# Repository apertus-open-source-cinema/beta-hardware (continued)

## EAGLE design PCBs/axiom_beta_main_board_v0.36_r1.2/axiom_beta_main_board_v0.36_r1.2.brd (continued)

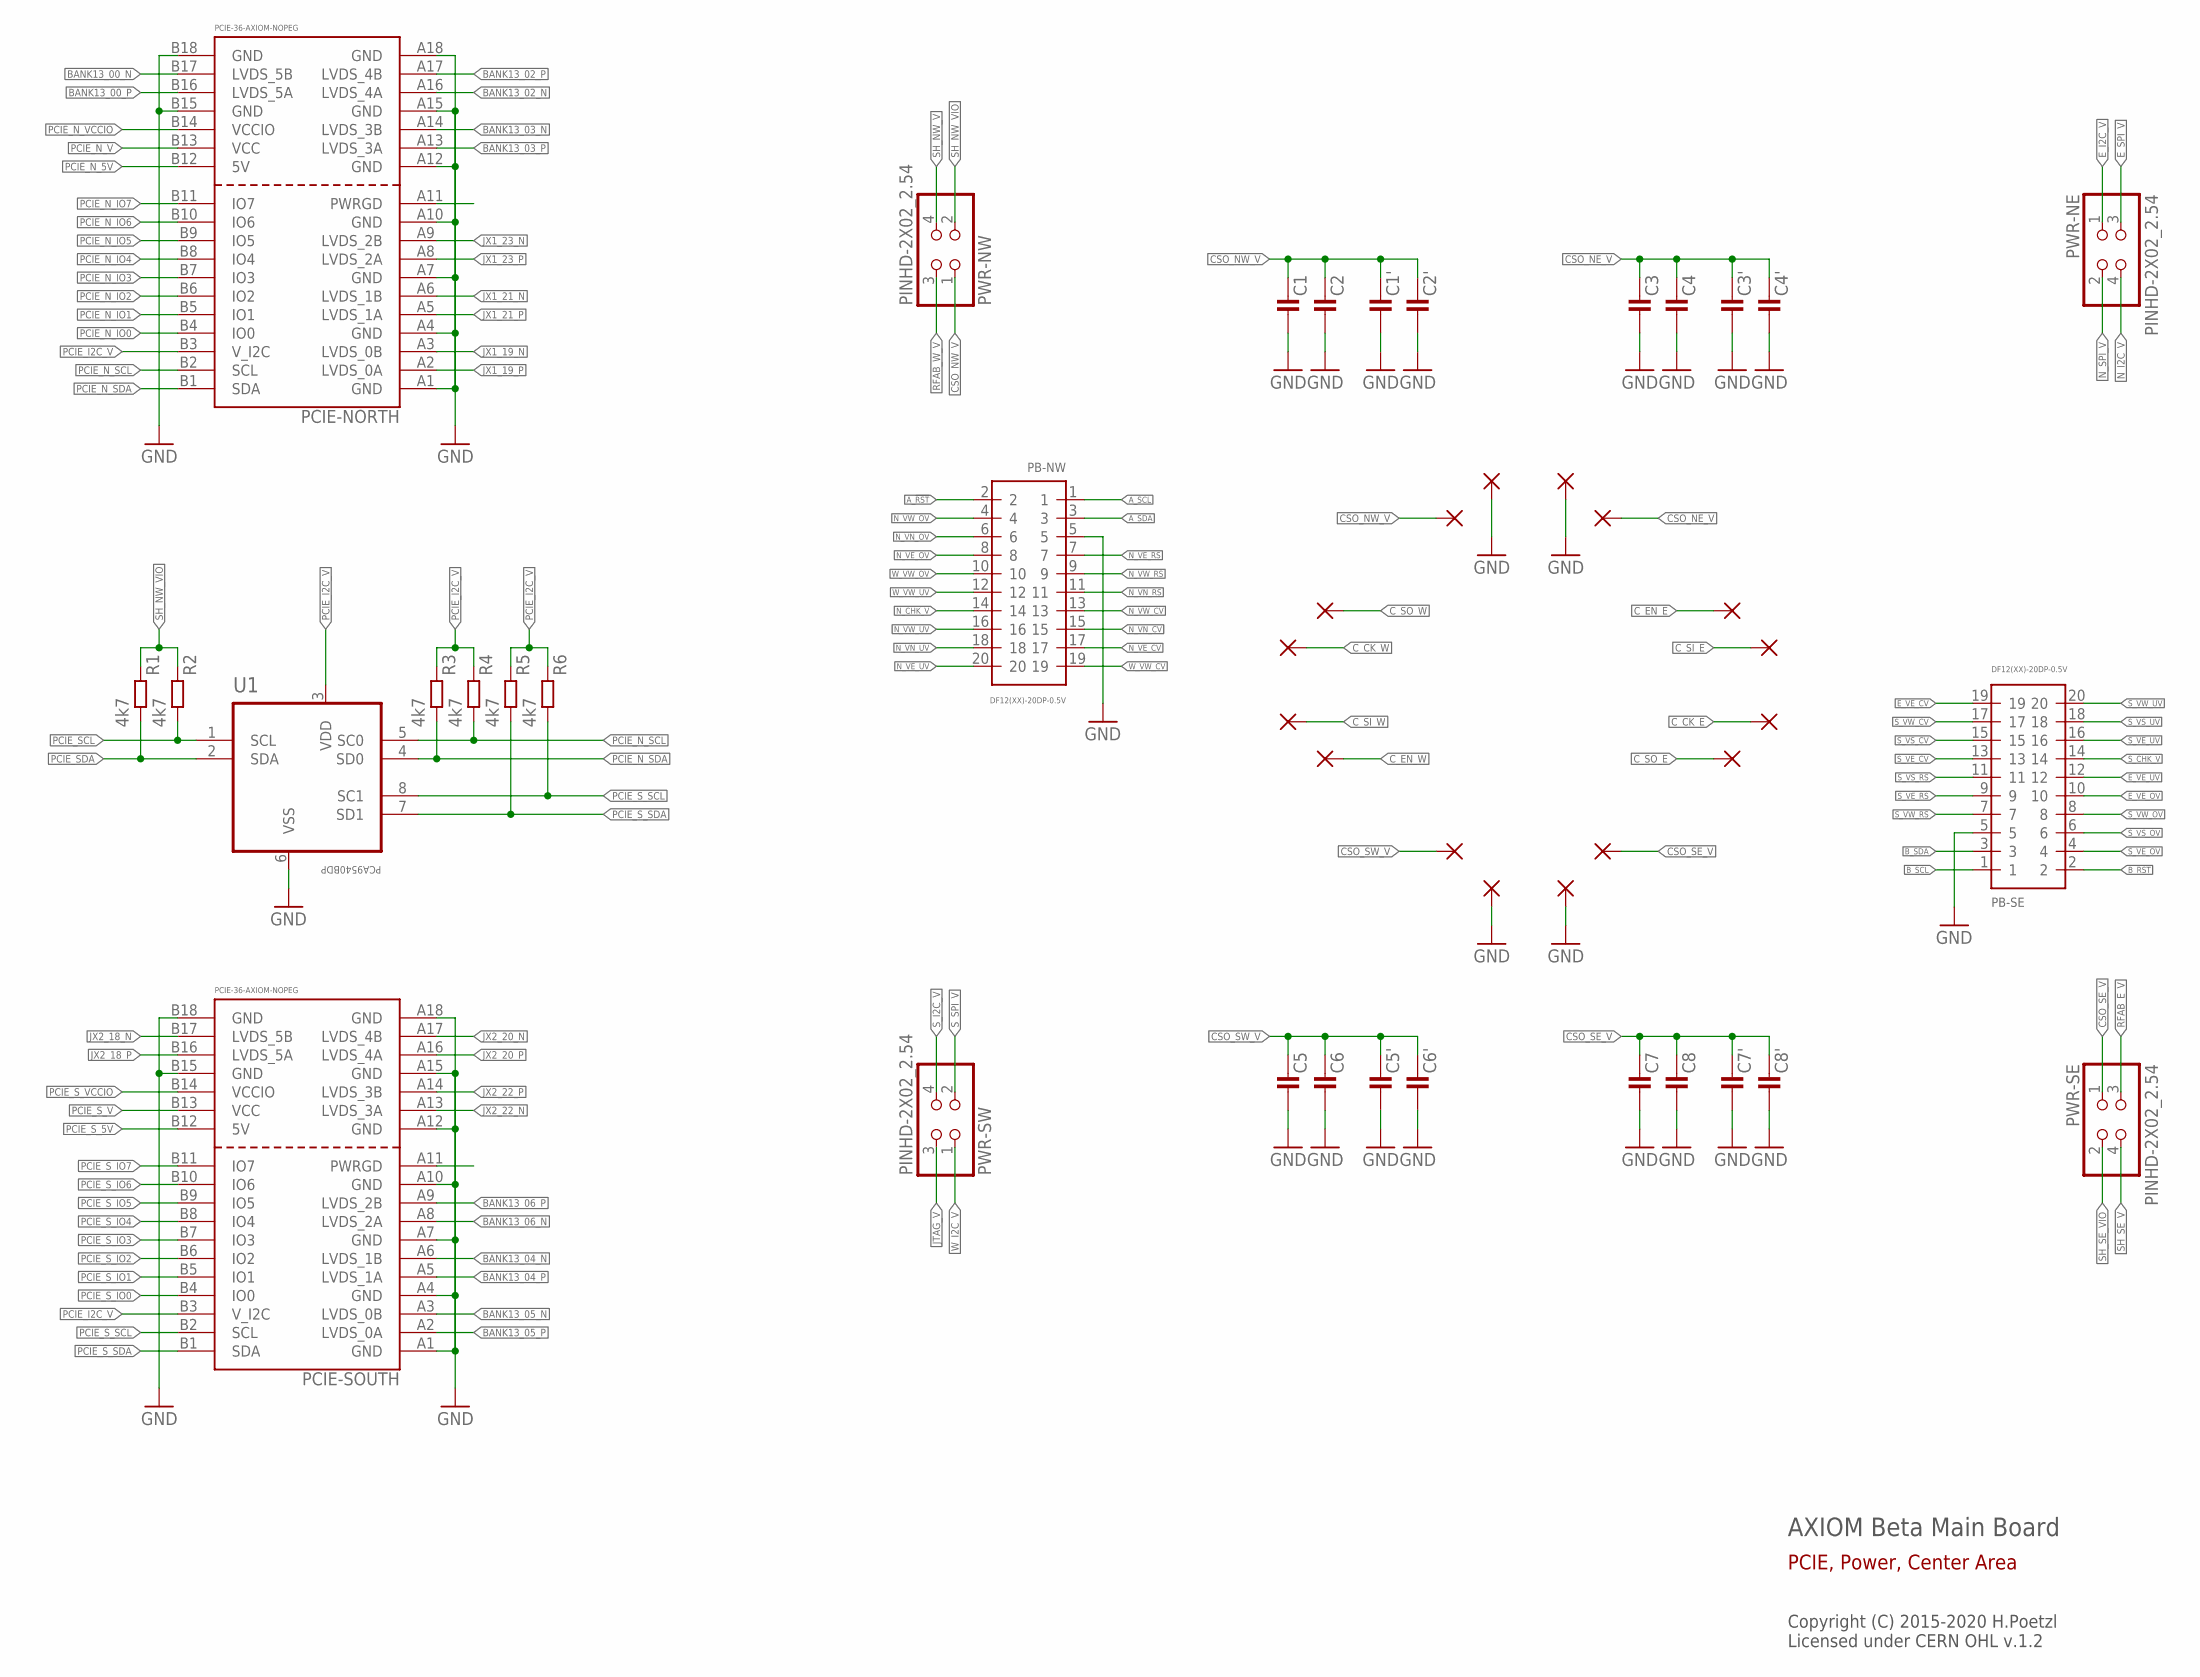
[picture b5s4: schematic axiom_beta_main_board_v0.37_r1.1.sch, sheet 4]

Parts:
C1, C1', C3, C3', C5, C5', C7, C7': C0805-A; 0805-A
C2, C2', C4, C4', C6, C6', C8, C8': C0603-A; 0603-A
PAD1, PAD2, PAD3, PAD4, PAD5, PAD6, PAD7, PAD8, PAD9, PAD10, PAD11, PAD12, PAD13, PAD14, PAD15, PAD16: PINPAD1.27MM; 1.2/0.6
PB-NW: DF12(XX)-20DP-0.5V
PB-SE: DF12(XX)-20DP-0.5V
PCIE-NORTH: PCIE-36-AXIOM-NOPEG; PCIE-36-NOPEG
PCIE-SOUTH: PCIE-36-AXIOM-NOPEG; PCIE-36-NOPEG
PWR-NE: PINHD-2X02_2.54; 2X02
PWR-NW: PINHD-2X02_2.54; 2X02
PWR-SE: PINHD-2X02_2.54; 2X02
PWR-SW: PINHD-2X02_2.54; 2X02
R1, R2, R3, R4, R5, R6: 4k7; 0402-B
U1: PCA9540BDP; SOP65P490X300-8N

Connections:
A_!RST: PB-NW.2; also elsewhere on the board
A_SCL: PB-NW.1; also elsewhere on the board
A_SDA: PB-NW.3; also elsewhere on the board
BANK13_00_N: PCIE-NORTH.B17 (LVDS_5B); also elsewhere on the board
BANK13_00_P: PCIE-NORTH.B16 (LVDS_5A); also elsewhere on the board
BANK13_02_N: PCIE-NORTH.A16 (LVDS_4A); also elsewhere on the board
BANK13_02_P: PCIE-NORTH.A17 (LVDS_4B); also elsewhere on the board
BANK13_03_N: PCIE-NORTH.A14 (LVDS_3B); also elsewhere on the board
BANK13_03_P: PCIE-NORTH.A13 (LVDS_3A); also elsewhere on the board
BANK13_04_N: PCIE-SOUTH.A6 (LVDS_1B); also elsewhere on the board
BANK13_04_P: PCIE-SOUTH.A5 (LVDS_1A); also elsewhere on the board
BANK13_05_N: PCIE-SOUTH.A3 (LVDS_0B); also elsewhere on the board
BANK13_05_P: PCIE-SOUTH.A2 (LVDS_0A); also elsewhere on the board
BANK13_06_N: PCIE-SOUTH.A8 (LVDS_2A); also elsewhere on the board
BANK13_06_P: PCIE-SOUTH.A9 (LVDS_2B); also elsewhere on the board
B_!RST: PB-SE.2; also elsewhere on the board
B_SCL: PB-SE.1; also elsewhere on the board
B_SDA: PB-SE.3; also elsewhere on the board
CSO_NE_V: C3.1, C3'.1, C4.1, C4'.1, PAD2.1; also elsewhere on the board
CSO_NW_V: C1.1, C1'.1, C2.1, C2'.1, PAD15.1, PWR-NW.1
CSO_SE_V: C7.1, C7'.1, C8.1, C8'.1, PAD7.1, PWR-SE.1
CSO_SW_V: C5.1, C5'.1, C6.1, C6'.1, PAD10.1; also elsewhere on the board
C_CK_E: PAD5.1; also elsewhere on the board
C_CK_W: PAD13.1; also elsewhere on the board
C_EN_E: PAD3.1; also elsewhere on the board
C_EN_W: PAD11.1; also elsewhere on the board
C_SI_E: PAD4.1; also elsewhere on the board
C_SI_W: PAD12.1; also elsewhere on the board
C_SO_E: PAD6.1; also elsewhere on the board
C_SO_W: PAD14.1; also elsewhere on the board
E_I2C_V: PWR-NE.1; also elsewhere on the board
E_SPI_V: PWR-NE.3; also elsewhere on the board
E_VE_CV: PB-SE.19; also elsewhere on the board
E_VE_OV: PB-SE.10; also elsewhere on the board
E_VE_UV: PB-SE.12; also elsewhere on the board
GND: C1.2, C1'.2, C2.2, C2'.2, C3.2, C3'.2, C4.2, C4'.2, C5.2, C5'.2, C6.2, C6'.2, C7.2, C7'.2, C8.2, C8'.2, PAD1.1, PAD8.1, PAD9.1, PAD16.1, PB-NW.5, PB-SE.5, PCIE-NORTH.A1 (GND), PCIE-NORTH.A4 (GND), PCIE-NORTH.A7 (GND), PCIE-NORTH.A10 (GND), PCIE-NORTH.A12 (GND), PCIE-NORTH.A15 (GND), PCIE-NORTH.A18 (GND), PCIE-NORTH.B15 (GND), PCIE-NORTH.B18 (GND), PCIE-SOUTH.A1 (GND), PCIE-SOUTH.A4 (GND), PCIE-SOUTH.A7 (GND), PCIE-SOUTH.A10 (GND), PCIE-SOUTH.A12 (GND), PCIE-SOUTH.A15 (GND), PCIE-SOUTH.A18 (GND), PCIE-SOUTH.B15 (GND), PCIE-SOUTH.B18 (GND), U1.6 (VSS); also elsewhere on the board
JTAG_V: PWR-SW.3; also elsewhere on the board
JX1_19_N: PCIE-NORTH.A3 (LVDS_0B); also elsewhere on the board
JX1_19_P: PCIE-NORTH.A2 (LVDS_0A); also elsewhere on the board
JX1_21_N: PCIE-NORTH.A6 (LVDS_1B); also elsewhere on the board
JX1_21_P: PCIE-NORTH.A5 (LVDS_1A); also elsewhere on the board
JX1_23_N: PCIE-NORTH.A9 (LVDS_2B); also elsewhere on the board
JX1_23_P: PCIE-NORTH.A8 (LVDS_2A); also elsewhere on the board
JX2_18_N: PCIE-SOUTH.B17 (LVDS_5B); also elsewhere on the board
JX2_18_P: PCIE-SOUTH.B16 (LVDS_5A); also elsewhere on the board
JX2_20_N: PCIE-SOUTH.A17 (LVDS_4B); also elsewhere on the board
JX2_20_P: PCIE-SOUTH.A16 (LVDS_4A); also elsewhere on the board
JX2_22_N: PCIE-SOUTH.A13 (LVDS_3A); also elsewhere on the board
JX2_22_P: PCIE-SOUTH.A14 (LVDS_3B); also elsewhere on the board
N_CHK_V: PB-NW.14; also elsewhere on the board
N_I2C_V: PWR-NE.4; also elsewhere on the board
N_SPI_V: PWR-NE.2; also elsewhere on the board
N_VE_CV: PB-NW.17; also elsewhere on the board
N_VE_OV: PB-NW.8; also elsewhere on the board
N_VE_RS: PB-NW.7; also elsewhere on the board
N_VE_UV: PB-NW.20; also elsewhere on the board
N_VN_CV: PB-NW.15; also elsewhere on the board
N_VN_OV: PB-NW.6; also elsewhere on the board
N_VN_RS: PB-NW.11; also elsewhere on the board
N_VN_UV: PB-NW.18; also elsewhere on the board
N_VW_CV: PB-NW.13; also elsewhere on the board
N_VW_OV: PB-NW.4; also elsewhere on the board
N_VW_RS: PB-NW.9; also elsewhere on the board
N_VW_UV: PB-NW.16; also elsewhere on the board
PCIE_I2C_V: PCIE-NORTH.B3 (V_I2C), PCIE-SOUTH.B3 (V_I2C), R3.1, R4.1, R5.1, R6.1, U1.3 (VDD); also elsewhere on the board
PCIE_N_5V: PCIE-NORTH.B12 (5V); also elsewhere on the board
PCIE_N_IO0: PCIE-NORTH.B4 (IO0); also elsewhere on the board
PCIE_N_IO1: PCIE-NORTH.B5 (IO1); also elsewhere on the board
PCIE_N_IO2: PCIE-NORTH.B6 (IO2); also elsewhere on the board
PCIE_N_IO3: PCIE-NORTH.B7 (IO3); also elsewhere on the board
PCIE_N_IO4: PCIE-NORTH.B8 (IO4); also elsewhere on the board
PCIE_N_IO5: PCIE-NORTH.B9 (IO5); also elsewhere on the board
PCIE_N_IO6: PCIE-NORTH.B10 (IO6); also elsewhere on the board
PCIE_N_IO7: PCIE-NORTH.B11 (IO7); also elsewhere on the board
PCIE_N_SCL: PCIE-NORTH.B2 (SCL), R4.2, U1.5 (SC0)
PCIE_N_SDA: PCIE-NORTH.B1 (SDA), R3.2, U1.4 (SD0)
PCIE_N_V: PCIE-NORTH.B13 (VCC); also elsewhere on the board
PCIE_N_VCCIO: PCIE-NORTH.B14 (VCCIO); also elsewhere on the board
PCIE_SCL: R2.2, U1.1 (SCL); also elsewhere on the board
PCIE_SDA: R1.2, U1.2 (SDA); also elsewhere on the board
PCIE_S_5V: PCIE-SOUTH.B12 (5V); also elsewhere on the board
PCIE_S_IO0: PCIE-SOUTH.B4 (IO0); also elsewhere on the board
PCIE_S_IO1: PCIE-SOUTH.B5 (IO1); also elsewhere on the board
PCIE_S_IO2: PCIE-SOUTH.B6 (IO2); also elsewhere on the board
PCIE_S_IO3: PCIE-SOUTH.B7 (IO3); also elsewhere on the board
PCIE_S_IO4: PCIE-SOUTH.B8 (IO4); also elsewhere on the board
PCIE_S_IO5: PCIE-SOUTH.B9 (IO5); also elsewhere on the board
PCIE_S_IO6: PCIE-SOUTH.B10 (IO6); also elsewhere on the board
PCIE_S_IO7: PCIE-SOUTH.B11 (IO7); also elsewhere on the board
PCIE_S_SCL: PCIE-SOUTH.B2 (SCL), R6.2, U1.8 (SC1)
PCIE_S_SDA: PCIE-SOUTH.B1 (SDA), R5.2, U1.7 (SD1)
PCIE_S_V: PCIE-SOUTH.B13 (VCC); also elsewhere on the board
PCIE_S_VCCIO: PCIE-SOUTH.B14 (VCCIO); also elsewhere on the board
RFAB_E_V: PWR-SE.3; also elsewhere on the board
RFAB_W_V: PWR-NW.3; also elsewhere on the board
SH_NW_V: PWR-NW.4; also elsewhere on the board
SH_NW_VIO: PWR-NW.2, R1.1, R2.1; also elsewhere on the board
SH_SE_V: PWR-SE.4; also elsewhere on the board
SH_SE_VIO: PWR-SE.2; also elsewhere on the board
S_CHK_V: PB-SE.14; also elsewhere on the board
S_I2C_V: PWR-SW.4; also elsewhere on the board
S_SPI_V: PWR-SW.2; also elsewhere on the board
S_VE_CV: PB-SE.13; also elsewhere on the board
S_VE_OV: PB-SE.4; also elsewhere on the board
S_VE_RS: PB-SE.9; also elsewhere on the board
S_VE_UV: PB-SE.16; also elsewhere on the board
S_VS_CV: PB-SE.15; also elsewhere on the board
S_VS_OV: PB-SE.6; also elsewhere on the board
S_VS_RS: PB-SE.11; also elsewhere on the board
S_VS_UV: PB-SE.18; also elsewhere on the board
S_VW_CV: PB-SE.17; also elsewhere on the board
S_VW_OV: PB-SE.8; also elsewhere on the board
S_VW_RS: PB-SE.7; also elsewhere on the board
S_VW_UV: PB-SE.20; also elsewhere on the board
W_I2C_V: PWR-SW.1; also elsewhere on the board
W_VW_CV: PB-NW.19; also elsewhere on the board
W_VW_OV: PB-NW.10; also elsewhere on the board
W_VW_UV: PB-NW.12; also elsewhere on the board

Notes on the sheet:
AXIOM Beta Main Board
Copyright (C) 2015-2020 H.Poetzl Licensed under CERN OHL v.1.2
PCIE, Power, Center Area

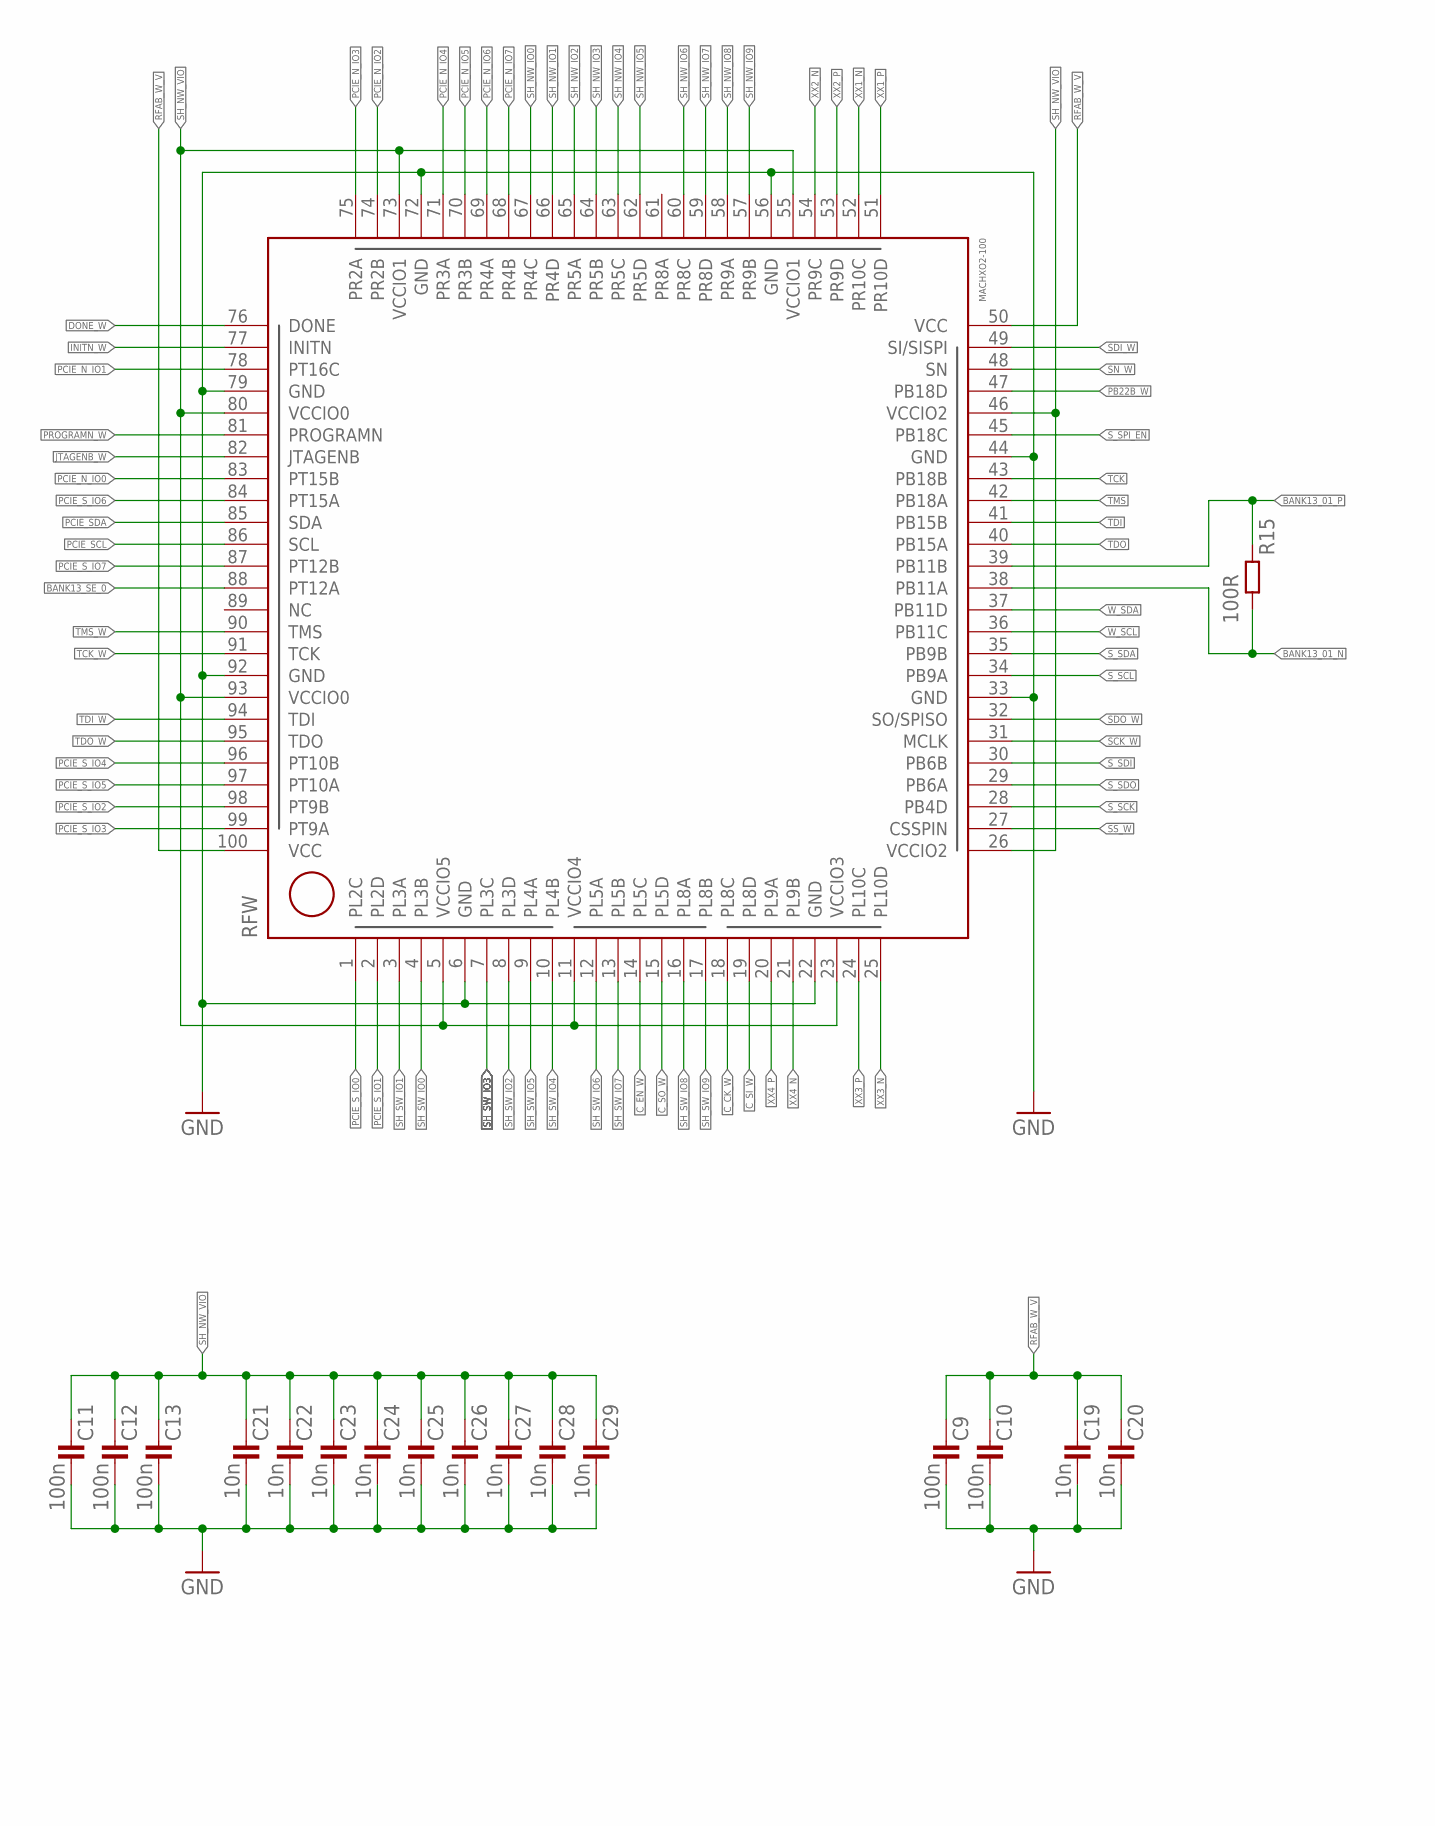
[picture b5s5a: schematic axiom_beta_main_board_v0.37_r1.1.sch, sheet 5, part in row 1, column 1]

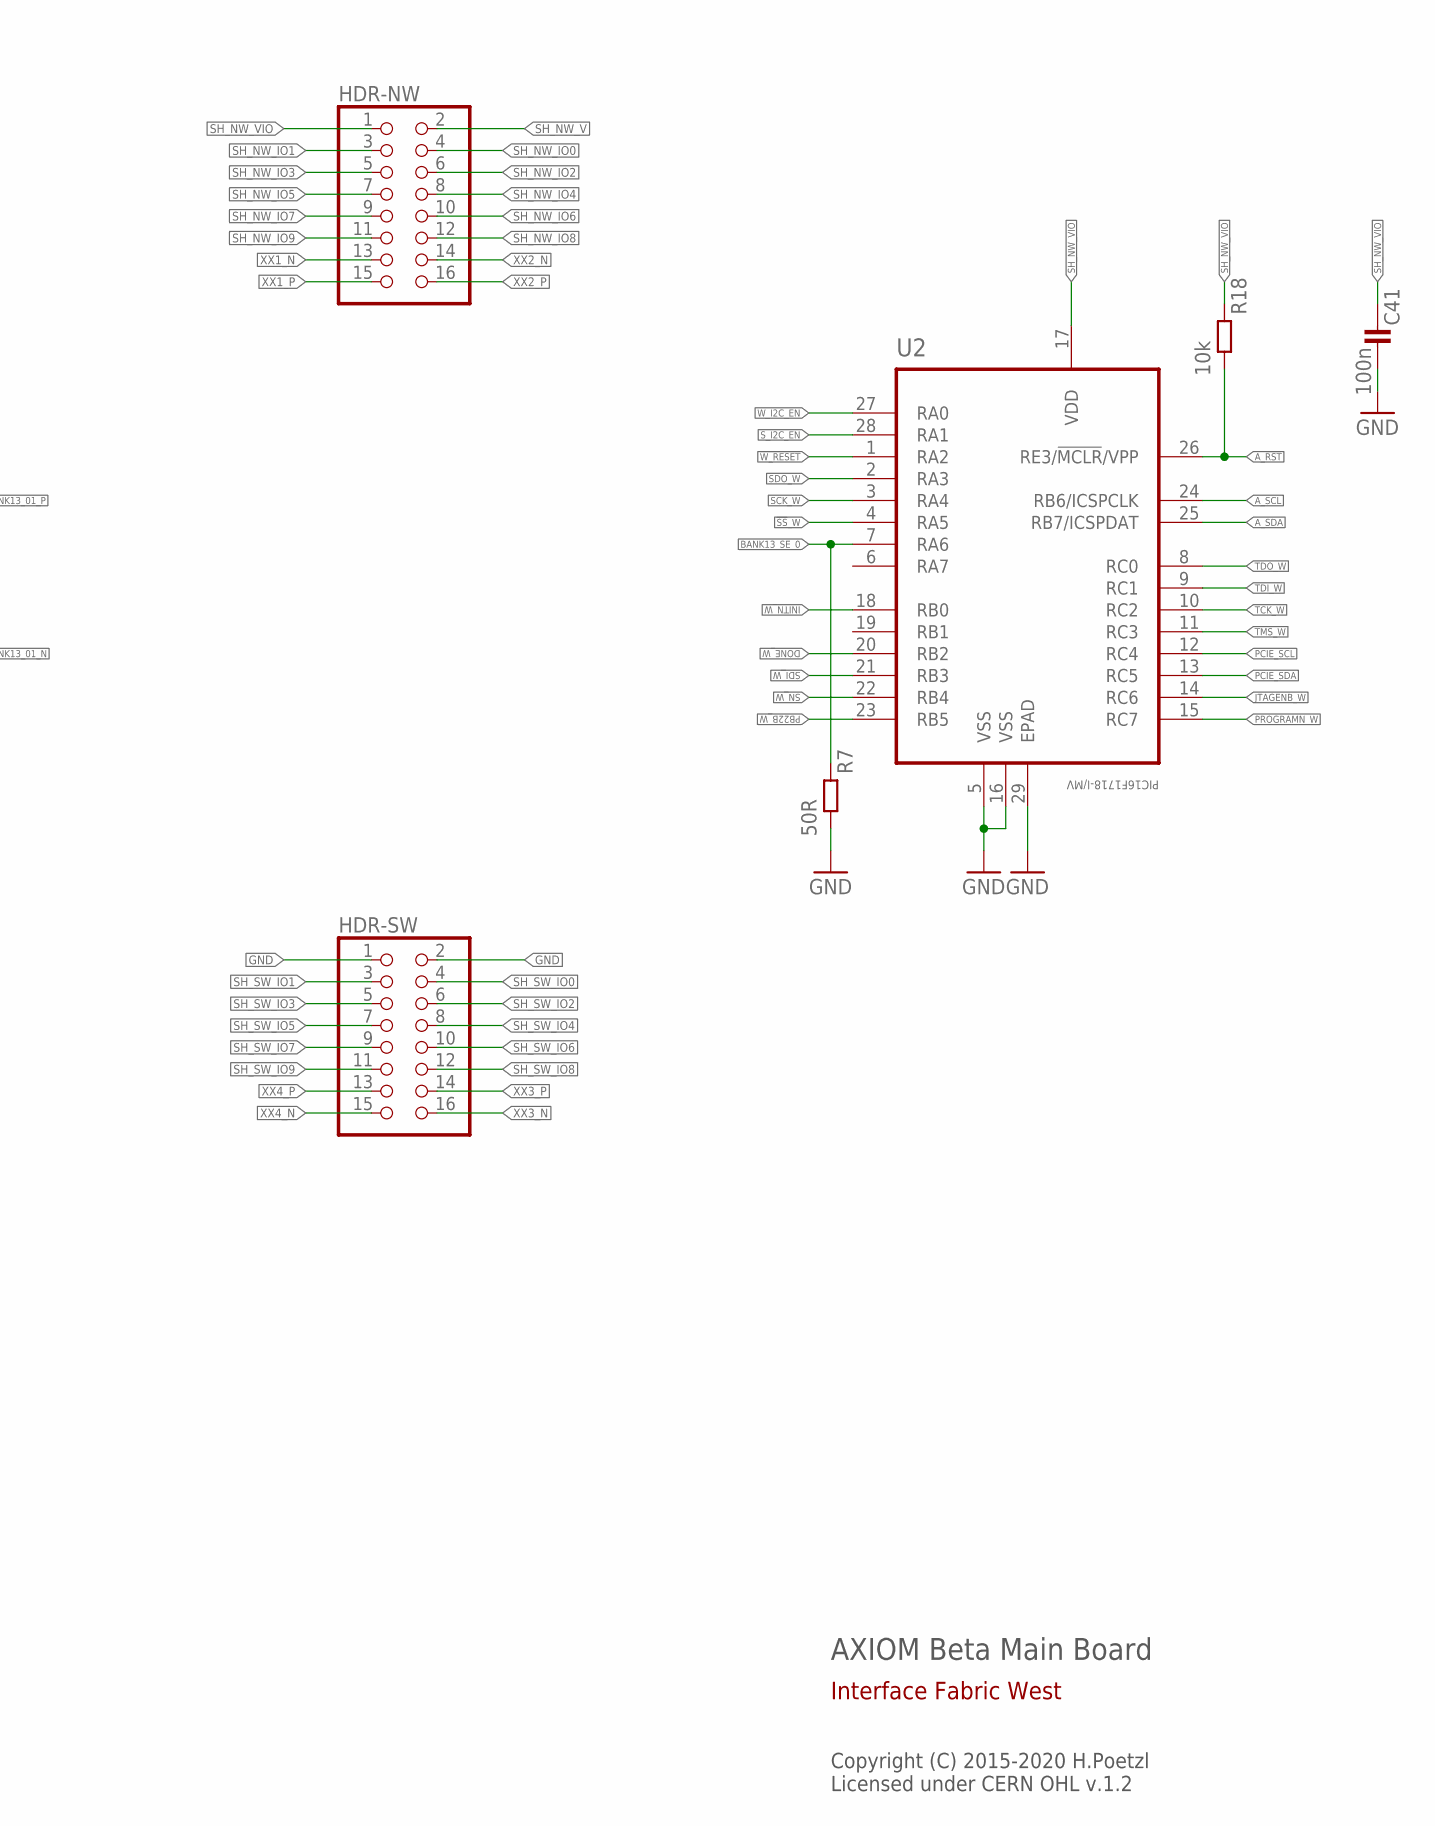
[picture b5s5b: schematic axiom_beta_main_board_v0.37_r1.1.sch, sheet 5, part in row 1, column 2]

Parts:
C9, C10, C11, C12, C13, C41: 100n; 0402-B
C19, C20, C21, C22, C23, C24, C25, C26, C27, C28, C29: 10n; 0402-B
HDR-NW: PINHD-2X08_2.00_LPR; 62101621821
HDR-SW: PINHD-2X08_2.00_LPR; 62101621821
R7: 50R; 0402-B
R15: 100R; 0201-B
R18: 10k; 0402-B
RFW: MACHXO2-100; MACHXO2-100TQFP
U2: PIC16F1718-I/MV; QFN40P400X400X55-29N

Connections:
!SS!_W: RFW.27 (CSSPIN), U2.4 (RA5)
!W_RESET!: U2.1 (RA2); also elsewhere on the board
A_!RST: R18.2, U2.26 (RE3/!MCLR!/VPP); also elsewhere on the board
A_SCL: U2.24 (RB6/ICSPCLK); also elsewhere on the board
A_SDA: U2.25 (RB7/ICSPDAT); also elsewhere on the board
BANK13_01_N: R15.2, RFW.38 (PB11A); also elsewhere on the board
BANK13_01_P: R15.1, RFW.39 (PB11B); also elsewhere on the board
BANK13_SE_0: R7.1, RFW.88 (PT12A), U2.7 (RA6); also elsewhere on the board
C_CK_W: RFW.18 (PL8C); also elsewhere on the board
C_EN_W: RFW.14 (PL5C); also elsewhere on the board
C_SI_W: RFW.19 (PL8D); also elsewhere on the board
C_SO_W: RFW.15 (PL5D); also elsewhere on the board
DONE_W: RFW.76 (DONE), U2.20 (RB2)
GND: C9.2, C10.2, C11.2, C12.2, C13.2, C19.2, C20.2, C21.2, C22.2, C23.2, C24.2, C25.2, C26.2, C27.2, C28.2, C29.2, C41.2, HDR-SW.1, HDR-SW.2, R7.2, RFW.6 (GND), RFW.22 (GND), RFW.33 (GND), RFW.44 (GND), RFW.56 (GND), RFW.72 (GND), RFW.79 (GND), RFW.92 (GND), U2.5 (VSS), U2.16 (VSS), U2.29 (EPAD); also elsewhere on the board
INITN_W: RFW.77 (INITN), U2.18 (RB0)
JTAGENB_W: RFW.82 (JTAGENB), U2.14 (RC6)
PB22B_W: RFW.47 (PB18D), U2.23 (RB5)
PCIE_N_IO0: RFW.83 (PT15B); also elsewhere on the board
PCIE_N_IO1: RFW.78 (PT16C); also elsewhere on the board
PCIE_N_IO2: RFW.74 (PR2B); also elsewhere on the board
PCIE_N_IO3: RFW.75 (PR2A); also elsewhere on the board
PCIE_N_IO4: RFW.71 (PR3A); also elsewhere on the board
PCIE_N_IO5: RFW.70 (PR3B); also elsewhere on the board
PCIE_N_IO6: RFW.69 (PR4A); also elsewhere on the board
PCIE_N_IO7: RFW.68 (PR4B); also elsewhere on the board
PCIE_SCL: RFW.86 (SCL), U2.12 (RC4); also elsewhere on the board
PCIE_SDA: RFW.85 (SDA), U2.13 (RC5); also elsewhere on the board
PCIE_S_IO0: RFW.1 (PL2C); also elsewhere on the board
PCIE_S_IO1: RFW.2 (PL2D); also elsewhere on the board
PCIE_S_IO2: RFW.98 (PT9B); also elsewhere on the board
PCIE_S_IO3: RFW.99 (PT9A); also elsewhere on the board
PCIE_S_IO4: RFW.96 (PT10B); also elsewhere on the board
PCIE_S_IO5: RFW.97 (PT10A); also elsewhere on the board
PCIE_S_IO6: RFW.84 (PT15A); also elsewhere on the board
PCIE_S_IO7: RFW.87 (PT12B); also elsewhere on the board
PROGRAMN_W: RFW.81 (PROGRAMN), U2.15 (RC7)
RFAB_W_V: C9.1, C10.1, C19.1, C20.1, RFW.50 (VCC), RFW.100 (VCC); also elsewhere on the board
SCK_W: RFW.31 (MCLK), U2.3 (RA4)
SDI_W: RFW.49 (SI/SISPI), U2.21 (RB3)
SDO_W: RFW.32 (SO/SPISO), U2.2 (RA3)
SH_NW_IO0: HDR-NW.4, RFW.67 (PR4C)
SH_NW_IO1: HDR-NW.3, RFW.66 (PR4D)
SH_NW_IO2: HDR-NW.6, RFW.65 (PR5A)
SH_NW_IO3: HDR-NW.5, RFW.64 (PR5B)
SH_NW_IO4: HDR-NW.8, RFW.63 (PR5C)
SH_NW_IO5: HDR-NW.7, RFW.62 (PR5D)
SH_NW_IO6: HDR-NW.10, RFW.60 (PR8C)
SH_NW_IO7: HDR-NW.9, RFW.59 (PR8D)
SH_NW_IO8: HDR-NW.12, RFW.58 (PR9A)
SH_NW_IO9: HDR-NW.11, RFW.57 (PR9B)
SH_NW_V: HDR-NW.2; also elsewhere on the board
SH_NW_VIO: C11.1, C12.1, C13.1, C21.1, C22.1, C23.1, C24.1, C25.1, C26.1, C27.1, C28.1, C29.1, C41.1, HDR-NW.1, R18.1, RFW.5 (VCCIO5), RFW.11 (VCCIO4), RFW.23 (VCCIO3), RFW.26 (VCCIO2), RFW.46 (VCCIO2), RFW.55 (VCCIO1), RFW.73 (VCCIO1), RFW.80 (VCCIO0), RFW.93 (VCCIO0), U2.17 (VDD); also elsewhere on the board
SH_SW_IO0: HDR-SW.4, RFW.4 (PL3B)
SH_SW_IO1: HDR-SW.3, RFW.3 (PL3A)
SH_SW_IO2: HDR-SW.6, RFW.8 (PL3D)
SH_SW_IO3: HDR-SW.5, RFW.7 (PL3C)
SH_SW_IO4: HDR-SW.8, RFW.10 (PL4B)
SH_SW_IO5: HDR-SW.7, RFW.9 (PL4A)
SH_SW_IO6: HDR-SW.10, RFW.12 (PL5A)
SH_SW_IO7: HDR-SW.9, RFW.13 (PL5B)
SH_SW_IO8: HDR-SW.12, RFW.16 (PL8A)
SH_SW_IO9: HDR-SW.11, RFW.17 (PL8B)
SN_W: RFW.48 (SN), U2.22 (RB4)
S_I2C_EN: U2.28 (RA1); also elsewhere on the board
S_SCK: RFW.28 (PB4D); also elsewhere on the board
S_SCL: RFW.34 (PB9A); also elsewhere on the board
S_SDA: RFW.35 (PB9B); also elsewhere on the board
S_SDI: RFW.30 (PB6B); also elsewhere on the board
S_SDO: RFW.29 (PB6A); also elsewhere on the board
S_SPI_EN: RFW.45 (PB18C); also elsewhere on the board
TCK: RFW.43 (PB18B); also elsewhere on the board
TCK_W: RFW.91 (TCK), U2.10 (RC2)
TDI: RFW.41 (PB15B); also elsewhere on the board
TDI_W: RFW.94 (TDI), U2.9 (RC1)
TDO: RFW.40 (PB15A); also elsewhere on the board
TDO_W: RFW.95 (TDO), U2.8 (RC0)
TMS: RFW.42 (PB18A); also elsewhere on the board
TMS_W: RFW.90 (TMS), U2.11 (RC3)
W_I2C_EN: U2.27 (RA0); also elsewhere on the board
W_SCL: RFW.36 (PB11C); also elsewhere on the board
W_SDA: RFW.37 (PB11D); also elsewhere on the board
XX1_N: HDR-NW.13, RFW.52 (PR10C)
XX1_P: HDR-NW.15, RFW.51 (PR10D)
XX2_N: HDR-NW.14, RFW.54 (PR9C)
XX2_P: HDR-NW.16, RFW.53 (PR9D)
XX3_N: HDR-SW.16, RFW.25 (PL10D)
XX3_P: HDR-SW.14, RFW.24 (PL10C)
XX4_N: HDR-SW.15, RFW.21 (PL9B)
XX4_P: HDR-SW.13, RFW.20 (PL9A)

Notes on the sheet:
AXIOM Beta Main Board
Copyright (C) 2015-2020 H.Poetzl Licensed under CERN OHL v.1.2
Interface Fabric West

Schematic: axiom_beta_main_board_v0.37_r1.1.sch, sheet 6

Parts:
C14, C15, C16, C17, C18, C42: 100n; 0402-B
C30, C31, C32, C33, C34, C35, C36, C37, C38, C39, C40: 10n; 0402-B
HDR-NE: PINHD-2X08_2.00_LPR; 62101621821
HDR-SE: PINHD-2X08_2.00_LPR; 62101621821
R8: 50R; 0402-B
R16, R17: 100R; 0201-B
R19: 10k; 0402-B
RFE: MACHXO2-100; MACHXO2-100TQFP
U3: PIC16F1718-I/MV; QFN40P400X400X55-29N

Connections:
!E_RESET!: U3.1 (RA2); also elsewhere on the board
!SS!_E: RFE.27 (CSSPIN), U3.4 (RA5)
B_!RST: R19.2, U3.26 (RE3/!MCLR!/VPP); also elsewhere on the board
B_SCL: U3.24 (RB6/ICSPCLK); also elsewhere on the board
B_SDA: U3.25 (RB7/ICSPDAT); also elsewhere on the board
C_CK_E: RFE.18 (PL8C); also elsewhere on the board
C_EN_E: RFE.14 (PL5C); also elsewhere on the board
C_SI_E: RFE.19 (PL8D); also elsewhere on the board
C_SO_E: RFE.15 (PL5D); also elsewhere on the board
DONE_E: RFE.76 (DONE), U3.20 (RB2)
E_EN: RFE.20 (PL9A); also elsewhere on the board
E_I2C_EN: U3.27 (RA0); also elsewhere on the board
E_IO0: RFE.99 (PT9A)
E_IO1: RFE.98 (PT9B)
E_IO2: RFE.97 (PT10A)
E_IO3: RFE.96 (PT10B)
E_IO5: RFE.87 (PT12B)
E_IO6: RFE.84 (PT15A)
E_IO7: RFE.83 (PT15B)
E_SCK: RFE.21 (PL9B); also elsewhere on the board
E_SCL: RFE.36 (PB11C); also elsewhere on the board
E_SDA: RFE.37 (PB11D); also elsewhere on the board
E_SDI: RFE.24 (PL10C); also elsewhere on the board
E_SDO: RFE.25 (PL10D); also elsewhere on the board
GND: C14.2, C15.2, C16.2, C17.2, C18.2, C30.2, C31.2, C32.2, C33.2, C34.2, C35.2, C36.2, C37.2, C38.2, C39.2, C40.2, C42.2, HDR-NE.1, HDR-NE.2, R8.2, RFE.6 (GND), RFE.22 (GND), RFE.33 (GND), RFE.44 (GND), RFE.56 (GND), RFE.72 (GND), RFE.79 (GND), RFE.92 (GND), U3.5 (VSS), U3.16 (VSS), U3.29 (EPAD); also elsewhere on the board
INITN_E: RFE.77 (INITN), U3.18 (RB0)
IO_SCL: RFE.86 (SCL), U3.12 (RC4)
IO_SDA: RFE.85 (SDA), U3.13 (RC5)
JTAGENB_E: RFE.82 (JTAGENB), U3.14 (RC6)
JX1_01_N: HDR-NE.13; also elsewhere on the board
JX1_01_P: HDR-NE.15; also elsewhere on the board
JX1_03_N: HDR-NE.14; also elsewhere on the board
JX1_03_P: HDR-NE.16; also elsewhere on the board
JX1_05_N: R16.2, RFE.35 (PB9B); also elsewhere on the board
JX1_05_P: R16.1, RFE.34 (PB9A); also elsewhere on the board
JX1_SE_0: R8.1, RFE.88 (PT12A), U3.7 (RA6); also elsewhere on the board
JX2_00_N: HDR-SE.14; also elsewhere on the board
JX2_00_P: HDR-SE.16; also elsewhere on the board
JX2_02_N: HDR-SE.13; also elsewhere on the board
JX2_02_P: HDR-SE.15; also elsewhere on the board
JX2_04_N: R17.1, RFE.38 (PB11A); also elsewhere on the board
JX2_04_P: R17.2, RFE.39 (PB11B); also elsewhere on the board
N_I2C_EN: U3.28 (RA1); also elsewhere on the board
N_IO0: RFE.1 (PL2C); also elsewhere on the board
N_IO1: RFE.2 (PL2D)
N_SCK: RFE.42 (PB18A); also elsewhere on the board
N_SCL: RFE.28 (PB4D); also elsewhere on the board
N_SDA: RFE.30 (PB6B); also elsewhere on the board
N_SDI: RFE.29 (PB6A); also elsewhere on the board
N_SDO: RFE.43 (PB18B); also elsewhere on the board
N_SPI_EN: RFE.45 (PB18C); also elsewhere on the board
PB22B_E: RFE.47 (PB18D), U3.23 (RB5)
PROGRAMN_E: RFE.81 (PROGRAMN), U3.15 (RC7)
RFAB_E_V: C14.1, C15.1, C30.1, C31.1, RFE.50 (VCC), RFE.100 (VCC); also elsewhere on the board
SCK_E: RFE.31 (MCLK), U3.3 (RA4)
SDI_E: RFE.49 (SI/SISPI), U3.21 (RB3)
SDO_E: RFE.32 (SO/SPISO), U3.2 (RA3)
SH_NE_IO0: HDR-NE.4, RFE.4 (PL3B)
SH_NE_IO1: HDR-NE.3, RFE.3 (PL3A)
SH_NE_IO2: HDR-NE.6, RFE.8 (PL3D)
SH_NE_IO3: HDR-NE.5, RFE.7 (PL3C)
SH_NE_IO4: HDR-NE.8, RFE.10 (PL4B)
SH_NE_IO5: HDR-NE.7, RFE.9 (PL4A)
SH_NE_IO6: HDR-NE.10, RFE.12 (PL5A)
SH_NE_IO7: HDR-NE.9, RFE.13 (PL5B)
SH_NE_IO8: HDR-NE.12, RFE.16 (PL8A)
SH_NE_IO9: HDR-NE.11, RFE.17 (PL8B)
SH_SE_IO0: HDR-SE.4, RFE.67 (PR4C)
SH_SE_IO1: HDR-SE.3, RFE.66 (PR4D)
SH_SE_IO2: HDR-SE.6, RFE.65 (PR5A)
SH_SE_IO3: HDR-SE.5, RFE.64 (PR5B)
SH_SE_IO4: HDR-SE.8, RFE.63 (PR5C)
SH_SE_IO5: HDR-SE.7, RFE.62 (PR5D)
SH_SE_IO6: HDR-SE.10, RFE.60 (PR8C)
SH_SE_IO7: HDR-SE.9, RFE.59 (PR8D)
SH_SE_IO8: HDR-SE.12, RFE.58 (PR9A)
SH_SE_IO9: HDR-SE.11, RFE.57 (PR9B)
SH_SE_V: HDR-SE.2; also elsewhere on the board
SH_SE_VIO: C16.1, C17.1, C18.1, C32.1, C33.1, C34.1, C35.1, C36.1, C37.1, C38.1, C39.1, C40.1, C42.1, HDR-SE.1, R19.1, RFE.5 (VCCIO5), RFE.11 (VCCIO4), RFE.23 (VCCIO3), RFE.26 (VCCIO2), RFE.46 (VCCIO2), RFE.55 (VCCIO1), RFE.73 (VCCIO1), RFE.80 (VCCIO0), RFE.93 (VCCIO0), U3.17 (VDD); also elsewhere on the board
SN_E: RFE.48 (SN), U3.22 (RB4)
S_IO0: RFE.75 (PR2A); also elsewhere on the board
S_IO1: RFE.74 (PR2B)
S_IO2: RFE.71 (PR3A)
S_IO3: RFE.70 (PR3B)
S_IO4: RFE.69 (PR4A)
S_IO5: RFE.68 (PR4B)
S_IO6: RFE.54 (PR9C)
S_IO7: RFE.53 (PR9D)
S_IO8: RFE.52 (PR10C)
S_IO9: RFE.51 (PR10D)
TCK_E: RFE.91 (TCK), U3.10 (RC2)
TDI_E: RFE.94 (TDI), U3.9 (RC1)
TDO_E: RFE.95 (TDO), U3.8 (RC0)
TMS_E: RFE.90 (TMS), U3.11 (RC3)

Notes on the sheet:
AXIOM Beta Main Board
Copyright (C) 2015-2020 H.Poetzl Licensed under CERN OHL v.1.2
Interface Fabric East

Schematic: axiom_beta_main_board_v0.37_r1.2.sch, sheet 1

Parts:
C43, C44: 10n; 0402-B
C45: 1u; 0402-B
D1: DB2S20500L; MICROMELF-R; FARNELL 2284949
FID1, FID2, FID3, FID4, FID5, FID6, FID7, FID8: FIDUCIAL; FID_ARROW
JP1: PINHD-1X02_2.00-90°-S; 1X02M/90-S
JP2: PINHD-1X02_2.00; 1X02M
JX1, JX2: BERGSTAK-61083F; 61083-FAKE
R9, R12: 10k; 0402-B
R10: 200k; 0402-B
R13, R14: 12R4; 0402-B
SP1: KSSG23J12
T1, T2: NX3008NBKT; SOT416
ZED1: µZ-FCI-NOHOLES-R; µZ-NOHOLES-R

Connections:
BANK13_SE_0: ZED1.200 (_0); also elsewhere on the board
CSO_NE_V: ZED1.7 (FPGA_VBAT); also elsewhere on the board
CSO_SW_V: ZED1.112 (VIN_HDR); also elsewhere on the board
DXP_0_N: ZED1.100 (_N)
DXP_0_P: ZED1.98 (_P)
GND: R12.1, T1.2 (S), T2.2 (S), ZED1.15 (GND), ZED1.16 (GND), ZED1.21 (GND), ZED1.22 (GND), ZED1.27 (GND), ZED1.28 (GND), ZED1.33 (GND), ZED1.34 (GND), ZED1.39 (GND), ZED1.40 (GND), ZED1.45 (GND), ZED1.46 (GND), ZED1.51 (GND), ZED1.52 (GND), ZED1.65 (GND), ZED1.66 (GND), ZED1.71 (GND), ZED1.72 (GND), ZED1.77 (GND), ZED1.85 (GND), ZED1.86 (GND), ZED1.95 (GND), ZED1.96 (GND), ZED1.115 (GND), ZED1.116 (GND), ZED1.121 (GND), ZED1.122 (GND), ZED1.127 (GND), ZED1.128 (GND), ZED1.133 (GND), ZED1.134 (GND), ZED1.139 (GND), ZED1.140 (GND), ZED1.145 (GND), ZED1.146 (GND), ZED1.151 (GND), ZED1.152 (GND), ZED1.165 (GND), ZED1.166 (GND), ZED1.171 (GND), ZED1.172 (GND), ZED1.177 (GND), ZED1.185 (GND), ZED1.186 (GND), ZED1.191 (GND), ZED1.192 (GND); also elsewhere on the board
JX1_SE_0: ZED1.9 (_0); also elsewhere on the board
JX1_SE_1: ZED1.10 (_1)
JX2_SE_0: ZED1.113 (_0)
JX2_SE_1: ZED1.114 (_1)
unnamed: C43.2, JP1.1, T1.3 (D)
unnamed: C44.2, R13.1, T2.3 (D)
unnamed: D1.C, R14.1
unnamed: D1.A, JP2.1, R13.2, SP1.2
unnamed: C43.1, R9.2, R10.2, T1.1 (G)
unnamed: C44.1, C45.1, R12.2, T2.1 (G)
N_IO0: R9.1; also elsewhere on the board
PCIE_I2C_V: ZED1.198 (VCCO_13); also elsewhere on the board
PCIE_N_5V: ZED1.59 (VIN_HDR), ZED1.60 (VIN_HDR); also elsewhere on the board
PCIE_N_V: ZED1.79 (VCCO_34), ZED1.80 (VCCO_34); also elsewhere on the board
PCIE_N_VCCIO: ZED1.78 (VCCO_34); also elsewhere on the board
PCIE_S_5V: ZED1.159 (VIN_HDR), ZED1.160 (VIN_HDR); also elsewhere on the board
PCIE_S_V: ZED1.179 (VCCO_35), ZED1.180 (VCCO_35); also elsewhere on the board
PCIE_S_VCCIO: ZED1.178 (VCCO_35); also elsewhere on the board
PEX_N_V: JP1.2, R10.1, ZED1.57 (VIN_HDR), ZED1.58 (VIN_HDR)
PEX_S_V: JP2.2, R14.2, SP1.1, ZED1.157 (VIN_HDR), ZED1.158 (VIN_HDR)
S_IO0: C45.2; also elsewhere on the board
VP_0_N: ZED1.99 (_N)
VP_0_P: ZED1.97 (_P)

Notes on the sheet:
AXIOM Beta Main Board
Copyright (C) 2014-2020 H.Poetzl Licensed under CERN OHL v.1.2
Power and Control Interface
